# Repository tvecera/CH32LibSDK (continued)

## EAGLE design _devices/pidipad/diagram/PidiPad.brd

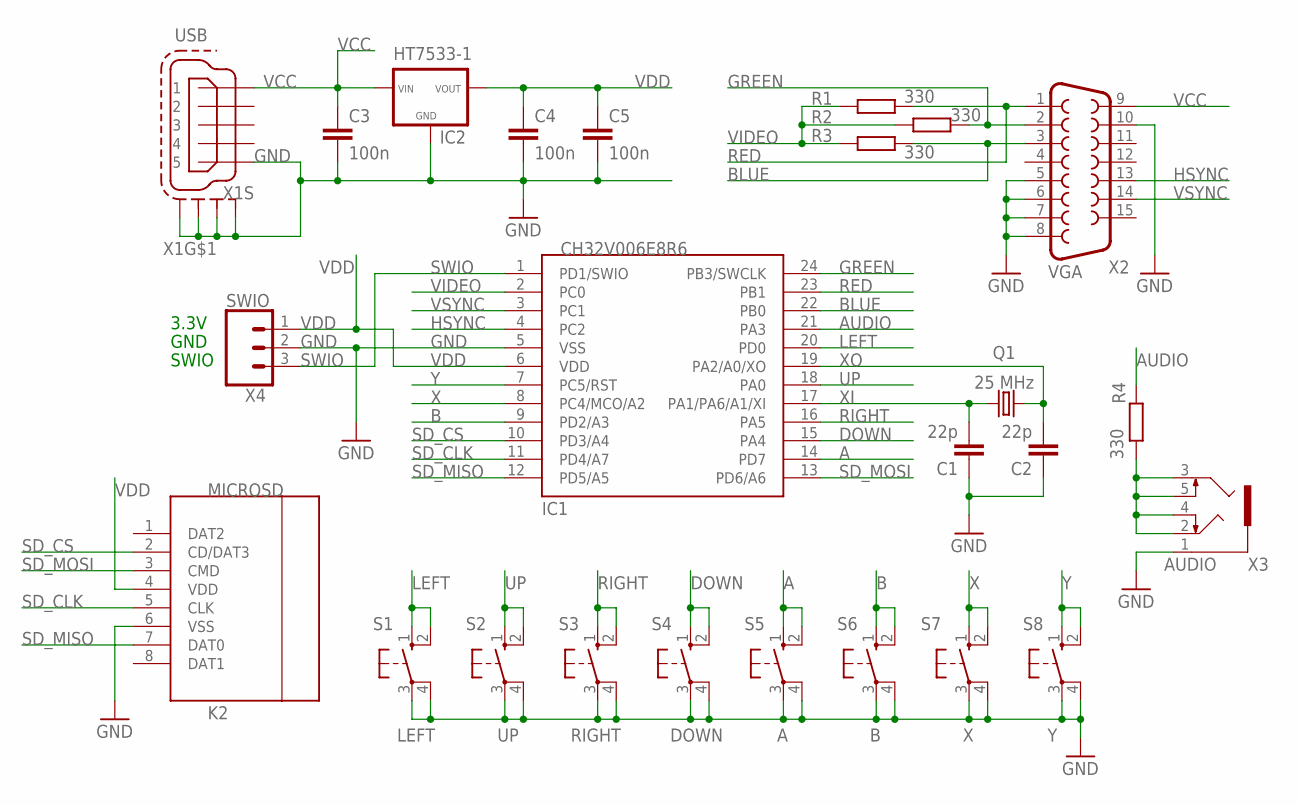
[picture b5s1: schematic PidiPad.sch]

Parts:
C1, C2: 22p; C050-024X044
C3, C4, C5: 100n; C050-024X044
IC1: CH32V006E8R6; QSOP24
IC2: HT7533-1
K2: MICROSD
Q1: 25 MHz; HC49U-V
R1, R2, R3, R4: 330; 0204/7
S1: LEFT; B3F-10XX
S2: UP; B3F-10XX
S3: RIGHT; B3F-10XX
S4: DOWN; B3F-10XX
S5: A; B3F-10XX
S6: B; B3F-10XX
S7: X; B3F-10XX
S8: Y; B3F-10XX
X1: USB; 32005-201
X2: VGA; HDF15H
X3: AUDIO; 1503_09
X4: SWIO; 1X03

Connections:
A: IC1.14 (PD7), S5.1 (S), S5.2 (S1)
AUDIO: IC1.21 (PA3), R4.2
B: IC1.9 (PD2/A3), S6.1 (S), S6.2 (S1)
BLUE: IC1.22 (PB0), R3.2, X2.3
DOWN: IC1.15 (PA4), S4.1 (S), S4.2 (S1)
GND: C1.1, C2.1, C3.2, C4.2, C5.2, IC1.5 (VSS), IC2.GND, K2.6 (VSS), S1.3, S1.4 (P1), S2.3, S2.4 (P1), S3.3, S3.4 (P1), S4.3, S4.4 (P1), S5.3, S5.4 (P1), S6.3, S6.4 (P1), S7.3, S7.4 (P1), S8.3, S8.4 (P1), X1.5, X1.M1 (S1), X1.M2 (S2), X1.M3 (S3), X1.M4 (S4), X2.5, X2.6, X2.7, X2.8, X2.10, X3.1, X4.2
GREEN: IC1.24 (PB3/SWCLK), R2.2, X2.2
HSYNC: IC1.4 (PC2), X2.13
LEFT: IC1.20 (PD0), S1.1 (S), S1.2 (S1)
unnamed: R4.1, X3.2, X3.3, X3.4, X3.5
RED: IC1.23 (PB1), R1.2, X2.1
RIGHT: IC1.16 (PA5), S3.1 (S), S3.2 (S1)
SD_CLK: IC1.11 (PD4/A7), K2.5 (CLK)
SD_CS: IC1.10 (PD3/A4), K2.2 (CD/DAT3)
SD_MISO: IC1.12 (PD5/A5), K2.7 (DAT0)
SD_MOSI: IC1.13 (PD6/A6), K2.3 (CMD)
SWIO: IC1.1 (PD1/SWIO), X4.3
UP: IC1.18 (PA0), S2.1 (S), S2.2 (S1)
VCC: C3.1, IC2.VIN, X1.1, X2.9
VDD: C4.1, C5.1, IC1.6 (VDD), IC2.VOUT, K2.4 (VDD), X4.1
VIDEO: IC1.2 (PC0), R1.1, R2.1, R3.1
VSYNC: IC1.3 (PC1), X2.14
X: IC1.8 (PC4/MCO/A2), S7.1 (S), S7.2 (S1)
XI: C1.2, IC1.17 (PA1/PA6/A1/XI), Q1.2
XO: C2.2, IC1.19 (PA2/A0/XO), Q1.1
Y: IC1.7 (PC5/RST), S8.1 (S), S8.2 (S1)

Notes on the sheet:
3.3V
GND
SWIO

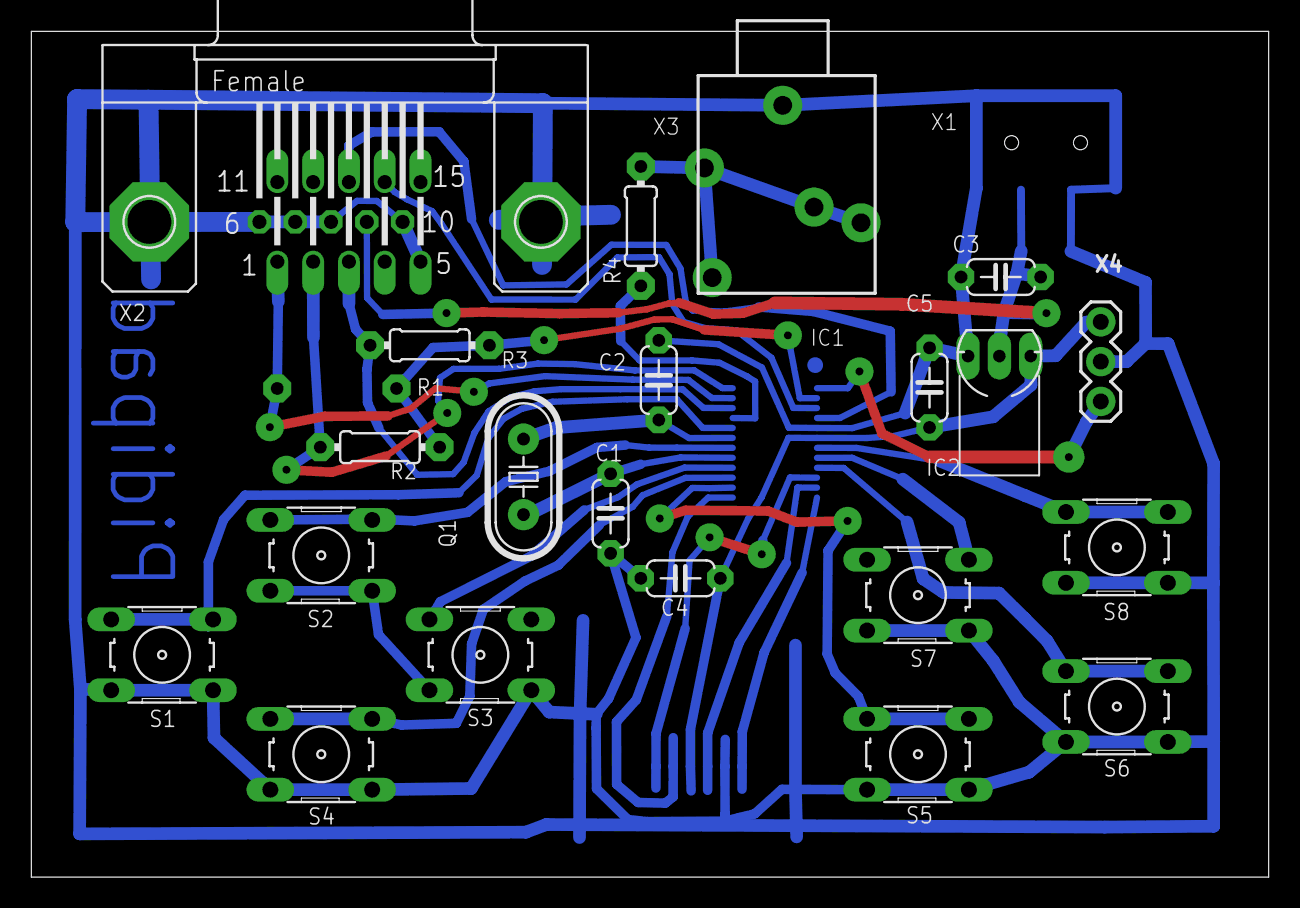
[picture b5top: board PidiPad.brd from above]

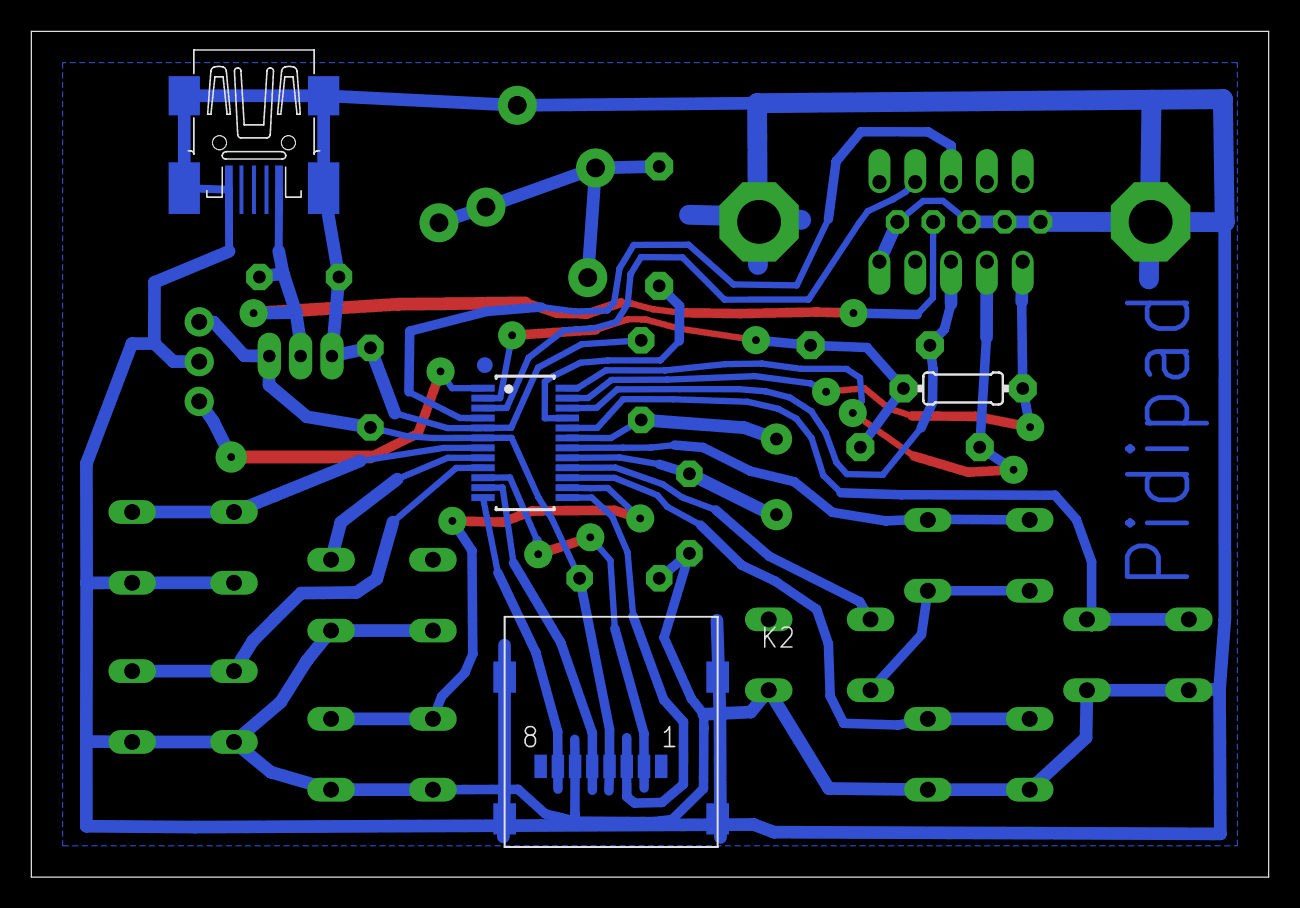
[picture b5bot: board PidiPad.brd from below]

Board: 2 copper layers, 79.0 x 54.0 mm, 25 parts (4 on the bottom side), 26 nets.

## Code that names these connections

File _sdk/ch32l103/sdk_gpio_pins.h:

// ****************************************************************************
//
//                              GPIO pins indices
//
// ****************************************************************************

#ifndef _SDK_GPIO_PINS_H
#define _SDK_GPIO_PINS_H

// GPIO port index
#define PORTA_INX	0
#define PORTB_INX	1
#define PORTC_INX	2
#define PORTD_INX	3

// GPIO index
#define PA0	(PORTA_INX*16)
#define PA1	(PA0+1)
#define PA2	(PA0+2)
#define PA3	(PA0+3)
#define PA4	(PA0+4)
#define PA5	(PA0+5)
#define PA6	(PA0+6)
#define PA7	(PA0+7)
#define PA8	(PA0+8)
#define PA9	(PA0+9)
#define PA10	(PA0+10)
#define PA11	(PA0+11)
#define PA12	(PA0+12)
#define PA13	(PA0+13)
#define PA14	(PA0+14)
#define PA15	(PA0+15)

#define PB0	(PORTB_INX*16)
#define PB1	(PB0+1)
#define PB2	(PB0+2)
#define PB3	(PB0+3)
#define PB4	(PB0+4)
#define PB5	(PB0+5)
#define PB6	(PB0+6)
#define PB7	(PB0+7)
#define PB8	(PB0+8)
#define PB9	(PB0+9)
#define PB10	(PB0+10)
#define PB11	(PB0+11)
#define PB12	(PB0+12)
#define PB13	(PB0+13)
#define PB14	(PB0+14)
#define PB15	(PB0+15)

#define PC0	(PORTC_INX*16)
#define PC1	(PC0+1)
#define PC2	(PC0+2)
#define PC3	(PC0+3)
#define PC4	(PC0+4)
#define PC5	(PC0+5)
#define PC6	(PC0+6)
#define PC7	(PC0+7)
#define PC8	(PC0+8)
#define PC9	(PC0+9)
#define PC10	(PC0+10)
#define PC11	(PC0+11)
#define PC12	(PC0+12)
#define PC13	(PC0+13)
#define PC14	(PC0+14)
#define PC15	(PC0+15)

#define PD0	(PORTD_INX*16)
#define PD1	(PD0+1)
#define PD2	(PD0+2)
#define PD3	(PD0+3)
#define PD4	(PD0+4)
#define PD5	(PD0+5)
#define PD6	(PD0+6)
#define PD7	(PD0+7)
#define PD8	(PD0+8)
#define PD9	(PD0+9)
#define PD10	(PD0+10)
#define PD11	(PD0+11)
#define PD12	(PD0+12)
#define PD13	(PD0+13)
#define PD14	(PD0+14)
#define PD15	(PD0+15)

// get port index from GPIO index
#define GPIO_PORTINX(gpio) ((gpio)>>4)

// get port pin from GPIO index
#define GPIO_PIN(gpio) ((gpio)&0x0f)

// compose GPIO index
#define GPIO_GPIO(port, pin) (((port)<<4)|(pin))

#endif // _SDK_GPIO_PINS_H

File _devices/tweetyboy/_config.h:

#define BOOTLOADER_SIZE	0x5000	// size of boot loader (20 KB; must be multiply of sector size 512 B)

// ----------------------------------------------------------------------------
//                             Device setup
// ----------------------------------------------------------------------------

// SPI display
// 0 ... PA4:CS, PA5:SCK, PA6:MISO, PA7:MOSI
// void GPIO_Remap_SPI1(int map);
#define DISP_SCK_GPIO	PA5	// SCK output to SPI display
#define DISP_MOSI_GPIO	PA7	// MOSI output to SPI display
#define DISP_RES_GPIO	PA12	// RES output to SPI display
#define DISP_DC_GPIO	PA13	// DC output to SPI display
#define DISP_CS_GPIO	PA4	// CS output to SPI display
#define DISP_BLK_GPIO	PB4	// BLK output to SPI display
#define DISP_SPI_MAP	0	// hardware display driver: display SPI mapping
#define DISP_SPI_DIV	1	// hardware display driver: display SPI baud divider 0..7 (means div=2..256)
#define DISP_SPEED	2	// software display driver: wait delay
#define DISP_GAMMA	2	// select display gamma curve 0..15

#ifndef USE_DISP
#define USE_DISP	2	// 1=use software display driver, 2=use hardware display driver (0=no driver)
#endif

// SD card GPIOs
#define SD_CS_GPIO	PB12	// CS output to SD card
#define SD_CLK_GPIO	PB9	// CLK output to SD card
#define SD_MISO_GPIO	PB8	// MISO input from SD card
#define SD_MOSI_GPIO	PB7	// MOSI output to SD card
#define SD_SPEED_INIT	(HCLK_PER_US*2)	// SD speed on init: wait delay "HCLK_PER_US*2" = 250 kbps
#define SD_SPEED_READ	(HCLK_PER_US/4)	// SD speed on read: wait delay "HCLK_PER_US/4" = 2 Mbps
#define SD_SPEED_WRITE	(HCLK_PER_US/1)	// SD speed on write: wait delay "HCLK_PER_US/1" = 500 kbps

#ifndef USE_SD
#define USE_SD		1	// 1=use SD card driver
#endif

#ifndef USE_DRAW
#define USE_DRAW	1	// 1=use graphics drawing functions
#endif

#ifndef USE_PRINT
#define USE_PRINT	1	// 1=use text printing functions
#endif

#ifndef USE_KEY
#define USE_KEY		1	// 1=use keyboard support
#endif

#ifndef USE_SOUND
#define USE_SOUND	2	// use sound support 1=tone, 2=melody
#endif

#ifndef USE_SCREENSHOT
#define USE_SCREENSHOT	0	// 1=use screen shot
#endif

#ifndef KEYCNT_REL
#define KEYCNT_REL	50	// keyboard counter - release interval in [ms]
#endif

#ifndef KEYCNT_PRESS
#define KEYCNT_PRESS	400	// keyboard counter - first repeat in [ms]
#endif

#ifndef KEYCNT_REPEAT
#define KEYCNT_REPEAT	100	// keyboard counter - next repeat in [ms]
#endif

#if USE_KEY			// 1=use keyboard support
#define SYSTICK_KEYSCAN	1	// 1=call KeyScan() function from SysTick system timer
#else
#define SYSTICK_KEYSCAN	0	// 1=call KeyScan() function from SysTick system timer
#endif

#if USE_SOUND == 2		// use sound support 1=tone, 2=melody
#define SYSTICK_SOUNDSCAN 1	// 1=call SoundScan() function fron SysTick system timer
#else
#define SYSTICK_SOUNDSCAN 0	// 1=call SoundScan() function fron SysTick system timer
#endif

// ----------------------------------------------------------------------------
//                            Library modules
// ----------------------------------------------------------------------------

#ifndef USE_CRC
#define USE_CRC		1	// 1=use CRC library
#endif

#ifndef USE_DECNUM
#define USE_DECNUM	1	// 1=use decode number
#endif

#ifndef USE_FAT
#define USE_FAT		1	// 1=use FAT filesystem
#endif

#ifndef USE_RAND
#define USE_RAND	1	// 1=use random number generator
#endif

// ----------------------------------------------------------------------------
//                             SDK modules
// ----------------------------------------------------------------------------

#ifndef USE_ADC
#define USE_ADC		1	// 1=use ADC peripheral
#endif

#ifndef USE_DMA
#define USE_DMA		1	// 1=use DMA peripheral
#endif

#ifndef USE_FLASH
#define USE_FLASH	1	// 1=use Flash programming
#endif

#ifndef USE_I2C
#define USE_I2C		1	// 1=use I2C peripheral
#endif

#ifndef USE_IRQ
#define USE_IRQ		1	// 1=use IRQ interrupt support
#endif

#ifndef USE_PWR
#define USE_PWR		1	// 1=use power control
#endif

#ifndef USE_SPI
#define USE_SPI		1	// 1=use SPI peripheral
#endif

#ifndef USE_TIM
#define USE_TIM		1	// 1=use timers
#endif

#ifndef USE_USART
#define USE_USART	1	// 1=use USART peripheral
#endif

// ----------------------------------------------------------------------------
//                            Clock Setup
// ----------------------------------------------------------------------------

// frequency of HSI internal oscillator 48MHz
#ifndef HSI_VALUE
#define HSI_VALUE	48000000
#endif

// System clock divider: 1, 2, 3, 4, 5, 6, 7, 8, 16, 32, 64, 128, 256 (default 1)
#ifndef SYSCLK_DIV
#define SYSCLK_DIV	1
#endif

// ADC clock divider: 1-16 (default 1)
#ifndef ADCCLK_DIV
#define ADCCLK_DIV	8		// CH32V0: max. 24 MHz (48/8 = 6 MHz)
#endif

// number of HCLK clock cycles per 1 us (used with Wait functions)
// - If you want to change frequency of system clock run-time, use a variable instead of constant.
#ifndef HCLK_PER_US
#define HCLK_PER_US	48
#endif

// increment of system time in [ms] on SysTick interrupt (0=do not use SysTick interrupt)
#ifndef SYSTICK_MS
#define SYSTICK_MS	16
#endif

// ----------------------------------------------------------------------------
//                          Peripheral clock enable
// ----------------------------------------------------------------------------

// Periferals
#ifndef ENABLE_SRAM
#define ENABLE_SRAM	1		// SRAM enable
#endif

#ifndef ENABLE_FLASH
#define ENABLE_FLASH	1		// FLASH enable (needed to rewrite RESET function)
#endif

#ifndef ENABLE_WWDG
#define ENABLE_WWDG	0		// Window watchdog enable
#endif

#ifndef ENABLE_PWR
#define ENABLE_PWR	1		// Power module enable
#endif

#ifndef ENABLE_AFI
#define ENABLE_AFI	1		// I/O auxiliary function enable
#endif

#ifndef ENABLE_PA
#define ENABLE_PA	1		// PA port enable
#endif

#ifndef ENABLE_PB
#define ENABLE_PB	1		// PB port enable
#endif

#ifndef ENABLE_PC
#define ENABLE_PC	1		// PC port enable
#endif

#ifndef ENABLE_ADC1
#define ENABLE_ADC1	1		// ADC1 module enable
#endif

#ifndef ENABLE_TIM1
#define ENABLE_TIM1	1		// TIM1 module enable
#endif

#ifndef ENABLE_TIM2
#define ENABLE_TIM2	1		// TIM2 module enable
#endif

#ifndef ENABLE_TIM3
#define ENABLE_TIM3	1		// TIM3 module enable
#endif

#ifndef ENABLE_SPI1
#define ENABLE_SPI1	1		// SPI1 module enable
#endif

#ifndef ENABLE_USART1
#define ENABLE_USART1	1		// USART1 module enable
#endif

#ifndef ENABLE_USART2
#define ENABLE_USART2	0		// USART2 module enable
#endif

#ifndef ENABLE_USART3
#define ENABLE_USART3	0		// USART3 module enable
#endif

#ifndef ENABLE_USART4
#define ENABLE_USART4	1		// USART4 module enable
#endif

#ifndef ENABLE_I2C1
#define ENABLE_I2C1	1		// I2C1 module enable
#endif

#ifndef ENABLE_USBFS
#define ENABLE_USBFS	0		// USBFS module enable
#endif

#ifndef ENABLE_USBPD
#define ENABLE_USBPD	0		// USBPD module enable
#endif

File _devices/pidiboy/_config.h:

#define BOOTLOADER_SIZE	0x5000	// size of boot loader (20 KB; must be multiply of sector size 512 B)

// ----------------------------------------------------------------------------
//                             Device setup
// ----------------------------------------------------------------------------

// display
#define DISP_I2C_ADDR	0x3C	// display I2C address
#define DISP_SDA_GPIO	PC1	// display gpio with SDA
#define DISP_SCL_GPIO	PC2	// display gpio with SCL
#define DISP_I2C_MAP	0	// hardware display driver: I2C mapping

#ifndef DISP_WAIT_CLK
#define DISP_WAIT_CLK	5	// software display driver: number of I2C wait clock (0 or more) ... DispUpdate() takes 2:10ms, 3-4:11ms, 10:26 ms
#endif

#ifndef DISP_SPEED_HZ
#define DISP_SPEED_HZ	750000	// hardware display driver: I2C speed in Hz ... DispUpdate() takes 3M:4ms, 2M:6ms, 1M:11ms, 500K:20ms
#endif

#ifndef USE_DISP
#define USE_DISP	1	// 1=use software display driver, 2=use hardware display driver (0=no driver)
#endif

// SD card GPIOs
#define SD_CS_GPIO	PC0	// CS output to SD card
#define SD_CLK_GPIO	PC5	// CLK output to SD card
#define SD_MISO_GPIO	PC7	// MISO input from SD card
#define SD_MOSI_GPIO	PC6	// MOSI output to SD card
#define SD_SPEED_INIT	(HCLK_PER_US*2)	// SD speed on init: wait delay "HCLK_PER_US*2" = 250 kbps
#define SD_SPEED_READ	(HCLK_PER_US/4)	// SD speed on read: wait delay "HCLK_PER_US/4" = 2 Mbps
#define SD_SPEED_WRITE	(HCLK_PER_US/1)	// SD speed on write: wait delay "HCLK_PER_US/1" = 500 kbps
#define SD_SPI_MAP	1	// hardware SD card driver: SPI mapping
#define SD_SPI_DIV_INIT	7	// hardware SD card driver: SPI baud divider 0..7 (means div=2..256) on init
#define SD_SPI_DIV_READ	4	// hardware SD card driver: SPI baud divider 0..7 (means div=2..256) on read
#define SD_SPI_DIV_WRITE 6	// hardware SD card driver: SPI baud divider 0..7 (means div=2..256) on write

#ifndef USE_SD
#define USE_SD		1	// 1=use software SD card driver, 2=use hardware SD card driver (0=no driver)
#endif

#ifndef USE_DRAW
#define USE_DRAW	1	// 1=use graphics drawing functions
#endif

#ifndef USE_PRINT
#define USE_PRINT	1	// 1=use text printing functions
#endif

#ifndef USE_KEY
#define USE_KEY		1	// 1=use keyboard support
#endif

#ifndef USE_SOUND
#define USE_SOUND	1	// use sound support 1=tone, 2=melody
#endif

#ifndef USE_SCREENSHOT
#define USE_SCREENSHOT	0	// 1=use screen shot
#endif

#ifndef KEYCNT_REL
#define KEYCNT_REL	50	// keyboard counter - release interval in [ms]
#endif

#ifndef KEYCNT_PRESS
#define KEYCNT_PRESS	400	// keyboard counter - first repeat in [ms]
#endif

#ifndef KEYCNT_REPEAT
#define KEYCNT_REPEAT	100	// keyboard counter - next repeat in [ms]
#endif

#if USE_KEY			// 1=use keyboard support
#define SYSTICK_KEYSCAN	1	// 1=call KeyScan() function from SysTick system timer
#else
#define SYSTICK_KEYSCAN	0	// 1=call KeyScan() function from SysTick system timer
#endif

#if USE_SOUND == 2		// use sound support 1=tone, 2=melody
#define SYSTICK_SOUNDSCAN 1	// 1=call SoundScan() function fron SysTick system timer
#else
#define SYSTICK_SOUNDSCAN 0	// 1=call SoundScan() function fron SysTick system timer
#endif

// ----------------------------------------------------------------------------
//                            Library modules
// ----------------------------------------------------------------------------

#ifndef USE_CRC
#define USE_CRC		1	// 1=use CRC library
#endif

#ifndef USE_DECNUM
#define USE_DECNUM	1	// 1=use decode number
#endif

#ifndef USE_FAT
#define USE_FAT		1	// 1=use FAT filesystem
#endif

#ifndef USE_RAND
#define USE_RAND	1	// 1=use random number generator
#endif

// ----------------------------------------------------------------------------
//                             SDK modules
// ----------------------------------------------------------------------------

#ifndef USE_ADC
#define USE_ADC		1	// 1=use ADC peripheral
#endif

#ifndef USE_DMA
#define USE_DMA		1	// 1=use DMA peripheral
#endif

#ifndef USE_FLASH
#define USE_FLASH	1	// 1=use Flash programming
#endif

#ifndef USE_I2C
#define USE_I2C		1	// 1=use I2C peripheral
#endif

#ifndef USE_IRQ
#define USE_IRQ		1	// 1=use IRQ interrupt support
#endif

#ifndef USE_PWR
#define USE_PWR		1	// 1=use power control
#endif

#ifndef USE_SPI
#define USE_SPI		1	// 1=use SPI peripheral
#endif

#ifndef USE_TIM
#define USE_TIM		1	// 1=use timers
#endif

#ifndef USE_USART
#define USE_USART	1	// 1=use USART peripheral
#endif

// ----------------------------------------------------------------------------
//                            Clock Setup
// ----------------------------------------------------------------------------

// frequency of HSI internal oscillator 24MHz
#ifndef HSI_VALUE
#define HSI_VALUE	24000000
#endif

// System clock source: 1=HSI, 2=HSE, 3=HSE_Bypass, 4=PLL_HSI, 5=PLL_HSE, 6=PLL_HSE_Bypass, 7=PLL_HSI/2, 8=PLL_HSE/2, 9=PLL_HSE_Bypass/2
#ifndef SYSCLK_SRC
#define SYSCLK_SRC	4
#endif

// PLL multiplier
#ifndef PLLCLK_MUL
#define PLLCLK_MUL	2		// only *2 supported; 24 MHz * 2 = 48 MHz
#endif

// System clock divider: 1, 2, 3, 4, 5, 6, 7, 8, 16, 32, 64, 128, 256 (default 1)
#ifndef SYSCLK_DIV
#define SYSCLK_DIV	1
#endif

// ADC clock divider: (1,) 2, 4, 6, 8, 12, 16, 24, 32, 48, 64, 96, 128 (default 1 or 2)
#ifndef ADCCLK_DIV
#define ADCCLK_DIV	8		// CH32V0: max. 24 MHz (48 / 8 = 6 MHz)
#endif

// number of HCLK clock cycles per 1 us (used with Wait functions)
// - If you want to change frequency of system clock run-time, use a variable instead of constant.
#ifndef HCLK_PER_US
#define HCLK_PER_US	48
#endif

// increment of system time in [ms] on SysTick interrupt (0=do not use SysTick interrupt)
#ifndef SYSTICK_MS
#define SYSTICK_MS	16
#endif

// ----------------------------------------------------------------------------
//                          Peripheral clock enable
// ----------------------------------------------------------------------------

// Periferals
#ifndef ENABLE_SRAM
#define ENABLE_SRAM	1		// SRAM enable
#endif

#ifndef ENABLE_FLASH
#define ENABLE_FLASH	1		// FLASH enable (needed to rewrite RESET function)
#endif

#ifndef ENABLE_WWDG
#define ENABLE_WWDG	0		// Window watchdog enable
#endif

#ifndef ENABLE_PWR
#define ENABLE_PWR	1		// Power module enable
#endif

#ifndef ENABLE_AFI
#define ENABLE_AFI	1		// I/O auxiliary function enable
#endif

#ifndef ENABLE_PA
#define ENABLE_PA	1		// PA port enable
#endif

#ifndef ENABLE_PB
#define ENABLE_PB	1		// PB port enable
#endif

#ifndef ENABLE_PC
#define ENABLE_PC	1		// PC port enable
#endif

#ifndef ENABLE_PD
#define ENABLE_PD	1		// PD port enable
#endif

#ifndef ENABLE_ADC1
#define ENABLE_ADC1	1		// ADC1 module enable
#endif

#ifndef ENABLE_TIM1
#define ENABLE_TIM1	1		// TIM1 module enable
#endif

#ifndef ENABLE_TIM2
#define ENABLE_TIM2	1		// TIM2 module enable
#endif

#ifndef ENABLE_TIM3
#define ENABLE_TIM3	1		// TIM3 module enable
#endif

#ifndef ENABLE_SPI1
#define ENABLE_SPI1	1		// SPI1 module enable
#endif

#ifndef ENABLE_USART1
#define ENABLE_USART1	1		// USART1 module enable
#endif

#ifndef ENABLE_USART2
#define ENABLE_USART2	0		// USART2 module enable
#endif

#ifndef ENABLE_USART3
#define ENABLE_USART3	0		// USART3 module enable
#endif

#ifndef ENABLE_USART4
#define ENABLE_USART4	0		// USART4 module enable
#endif

#ifndef ENABLE_I2C1
#define ENABLE_I2C1	1		// I2C1 module enable
#endif

#ifndef ENABLE_USBFS
#define ENABLE_USBFS	0		// USBFS module enable
#endif

#ifndef ENABLE_USBPD
#define ENABLE_USBPD	0		// USBPD module enable
#endif

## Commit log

2025-06-20 v0.01
2025-06-21 Add Flappy
2025-06-25 init
2025-09-29 Add TinyBoy (CH32V003-GameConsole) device
    Add TinyBoy (CH32V003-GameConsole) device
2025-10-28 Add TinyBoy (CH32V003-GameConsole) device
2025-10-28 Add RVPC device
2025-11-25 Add RCA output for RVPC
